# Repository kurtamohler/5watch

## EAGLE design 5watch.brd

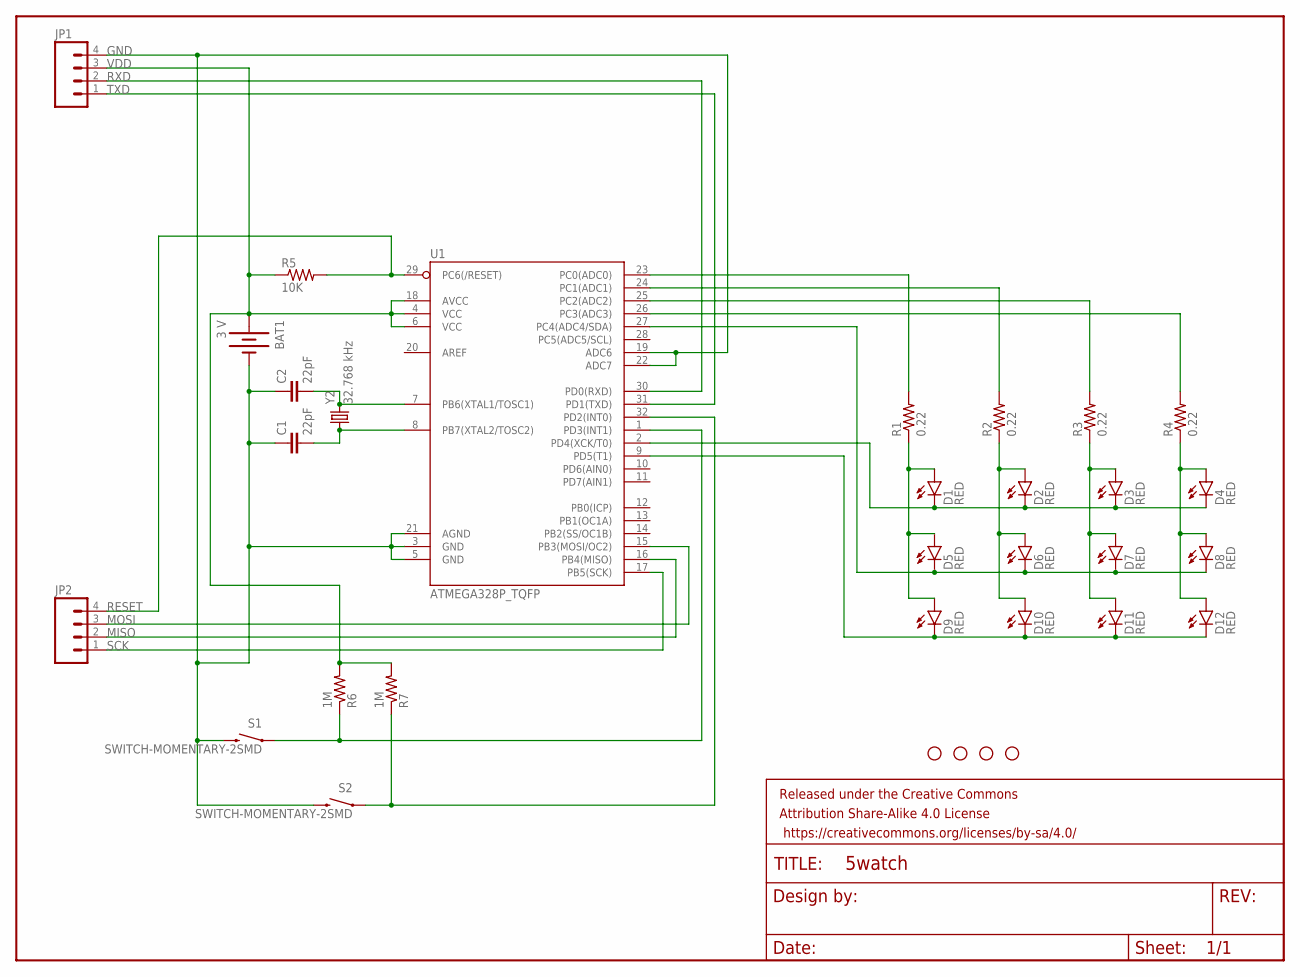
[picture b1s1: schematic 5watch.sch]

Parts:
BAT1: 3 V; BATTCON_20MM_4LEGS
C1, C2: 22pF; 0603-CAP
D1, D2, D3, D4, D5, D6, D7, D8, D9, D10, D11, D12: RED; LED-1206
FRAME1: FRAME-LETTER; CREATIVE_COMMONS
JP1, JP2: M04NO_SILK_ALL_ROUND; 1X04_NO_SILK_ALL_ROUND
R1, R2, R3, R4: 0.22; 0805
R5: 10K; 0603-RES
R6, R7: 1M; 0603-RES
S1, S2: SWITCH-MOMENTARY-2SMD; TACTILE-SWITCH-SMD
STANDOFF1, STANDOFF2, STANDOFF3, STANDOFF4: STAND-OFF
U1: ATMEGA328P_TQFP; TQFP32-08
Y2: 32.768 kHz; CRYSTAL-32KHZ-SMD

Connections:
GND: BAT1.2 (-), C1.1, C2.1, JP1.4, S1.3 (2), S2.3 (2), U1.3 (GND), U1.5 (GND), U1.19 (ADC6), U1.21 (AGND), U1.22 (ADC7)
MISO: JP2.2, U1.16 (PB4(MISO))
MOSI: JP2.3, U1.15 (PB3(MOSI/OC2))
unnamed: D2.A, D6.A, D10.A, R2.1
unnamed: D3.A, D7.A, D11.A, R3.1
unnamed: D4.A, D8.A, D12.A, R4.1
unnamed: D1.A, D5.A, D9.A, R1.1
unnamed: D1.C, D2.C, D3.C, D4.C, U1.2 (PD4(XCK/T0))
unnamed: D5.C, D6.C, D7.C, D8.C, U1.27 (PC4(ADC4/SDA))
unnamed: D9.C, D10.C, D11.C, D12.C, U1.9 (PD5(T1))
unnamed: C2.2, U1.7 (PB6(XTAL1/TOSC1)), Y2.X2 (2)
unnamed: R6.1, S1.1, U1.1 (PD3(INT1))
unnamed: C1.2, U1.8 (PB7(XTAL2/TOSC2)), Y2.X1 (1)
unnamed: R4.2, U1.26 (PC3(ADC3))
unnamed: R3.2, U1.25 (PC2(ADC2))
unnamed: R2.2, U1.24 (PC1(ADC1))
unnamed: R1.2, U1.23 (PC0(ADC0))
unnamed: R7.1, S2.1, U1.32 (PD2(INT0))
RESET: JP2.4, R5.2, U1.29 (PC6(/RESET))
RXD: JP1.2, U1.30 (PD0(RXD))
SCK: JP2.1, U1.17 (PB5(SCK))
TXD: JP1.1, U1.31 (PD1(TXD))
VDD: BAT1.1 (+), JP1.3, R5.1, R6.2, R7.2, U1.4 (VCC), U1.6 (VCC), U1.18 (AVCC)

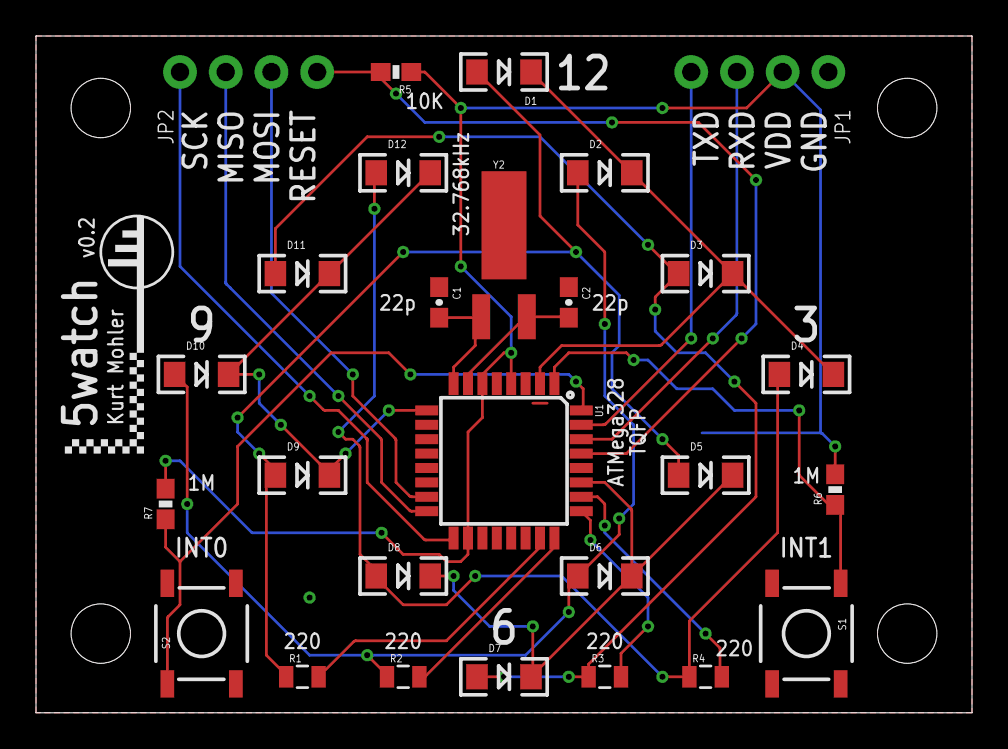
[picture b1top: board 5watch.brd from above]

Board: 2 copper layers, 52.0 x 37.6 mm, 33 parts (1 on the bottom side), 23 nets.

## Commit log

2016-01-19 first commit, v0.1
2016-01-25 fixed led connections, wired ADC6 and ADC7 to ground, removed TOSC pins from breakout, shrunk board, reversed button pin voltages
2016-01-25 moved traces around to increase ground fill connectivity
2016-01-25 moved silk prints around and added logo

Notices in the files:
parts and their libraries:
SparkFun-Electromechanical: Licensing: Creative Commons ShareAlike 4.0 International - https://creativecommons.org/licenses/by-sa/4.0
SparkFun-Aesthetics: Released under the Creative Commons Attribution Share-Alike 4.0 License
SparkFun-Aesthetics: https://creativecommons.org/licenses/by-sa/4.0
